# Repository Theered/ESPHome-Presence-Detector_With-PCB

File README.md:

# ESPHome-Presence-Detector_With-PCB
I was tired of my lights constantly turning off whenever I sat still while using a standard PIR motion detector. Since PIR sensors only detect "big movements", they often fail to notice someone who is sitting quietly.

To solve this, I built a presence detector using an mmWave sensor. Unlike a traditional PIR sensor, an mmWave sensor can detect very small movements, such as your chest moving while breathing, allowing it to reliably detect occupancy even when you're not moving around.

While designing the project, I decided to add a few extra features:

* **mmWave presence detection** for reliable occupancy sensing
* **PIR motion sensor** for fast motion detection when entering the room
* **Ambient light sensor** to prevent lights from turning on when the room is already bright
* **Status LED** to indicate Wi-Fi or device issues
* **Custom PCB** to keep the wiring clean and make assembly easier

The PCB connects all modules directly to the microcontroller, making installation as simple as plugging the sensors into their designated headers.

Sensor data is sent to Home Assistant using ESPHome, allowing you to create virtually any automation you can think of —from automatically controlling lights to sending notifications when someone enters a room, everything is possible.

## Requirements

Before starting this project, you will need:

1. A working Home Assistant server
2. A soldering iron and basic soldering skills
3. A bit of patience and a good mood ;)

**Note:** The status LED and its resistor are small and can be quite challenging to solder. If you don't care about the LED, it can be left out.

## PCB Design

schematic:

PCB:

## Design Inspiration

I wanted a clean and modern design for the detector, so i kindly asked chatGPT to make a few diffrent designes and shapes before settling on this final version:

i then started modeling my own...

## Project Status

🚧 This project is still under development.

Additional documentation will be added soon, including:

* Complete assembly guide
* ESPHome configuration- and firmware instalation guide
* refined 3D-printable enclosure files

Thank you for your patience while I finish building and documenting the project.

BOM:
1. ws2812b LED

2. TSL2591 IIC I2C Light Sensor

3. ESP32 S3 C3 SuperMini Development Board

5. HLK-LD2410c module

7. AM312 PIR motion detector

8. Female Straight Needle Pin Header

9. Custom PCB (gerber files are linked in the project)

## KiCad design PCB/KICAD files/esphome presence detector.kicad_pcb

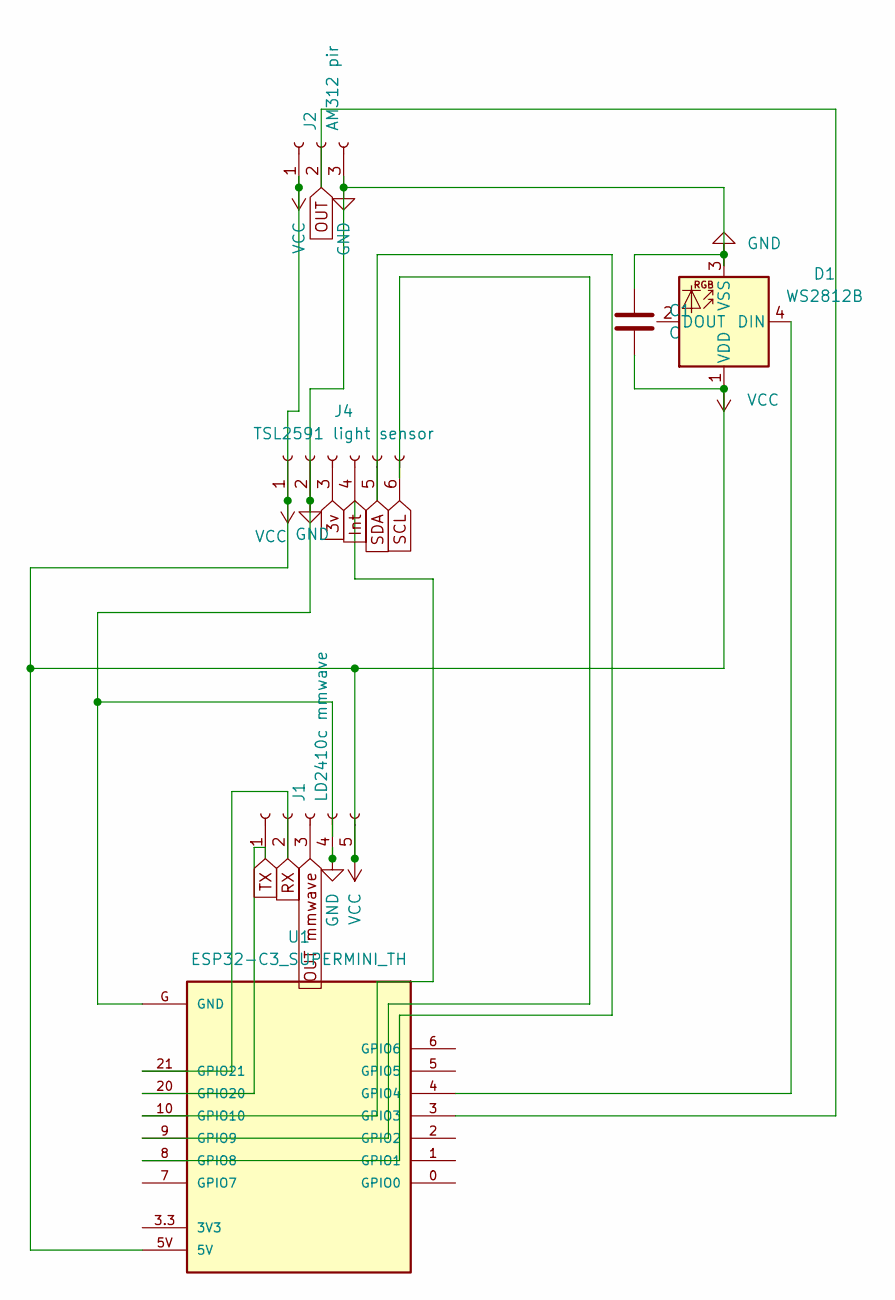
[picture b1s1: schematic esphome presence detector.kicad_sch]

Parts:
C1: C; C_0805_2012Metric_Pad1.18x1.45mm_HandSolder
D1: WS2812B; LED_WS2812B_PLCC4_5.0x5.0mm_P3.2mm
J1: LD2410c mmwave; PinSocket_1x05_P2.54mm_Vertical
J2: AM312 pir; PinSocket_1x03_P2.54mm_Vertical
J4: TSL2591 light sensor; PinSocket_1x06_P2.54mm_Vertical
U1: ESP32-C3_SUPERMINI_TH; MODULE_ESP32-C3_SUPERMINI_TH

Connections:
3v: J4.3
GND: C1.1, D1.3 (VSS), J1.4, J2.3, J4.2, U1.G (GND)
Int: J4.4, U1.10 (GPIO10)
unnamed: D1.4 (DIN), U1.4 (GPIO4)
OUT: J2.2, U1.3 (GPIO3)
OUT mmwave: J1.3
RX: J1.2, U1.21 (GPIO21)
SCL: J4.6
SDA: J4.5, U1.8 (GPIO8)
TX: J1.1, U1.20 (GPIO20)
VCC: C1.2, D1.1 (VDD), J1.5, J2.1, J4.1, U1.5V

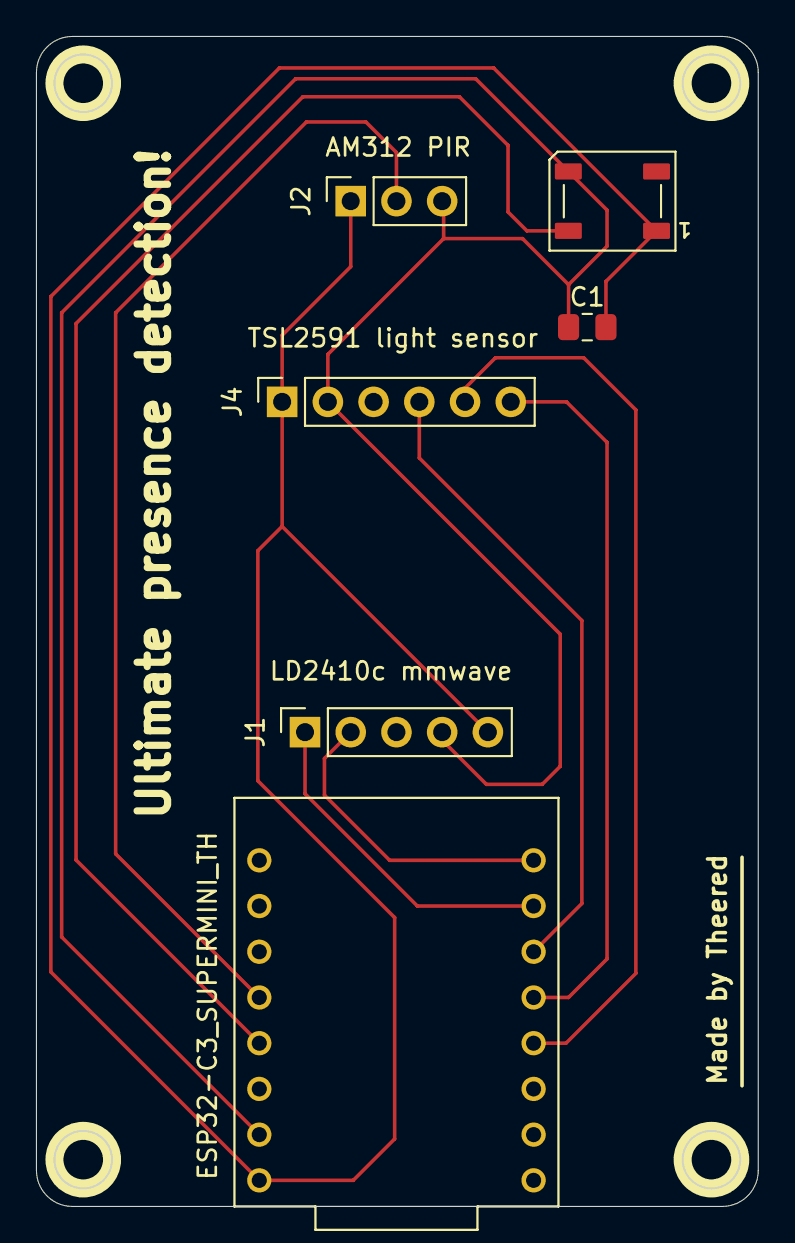
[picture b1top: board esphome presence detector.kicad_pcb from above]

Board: 2 copper layers, 40.1 x 64.9 mm, 6 parts (0 on the bottom side), 8 nets.

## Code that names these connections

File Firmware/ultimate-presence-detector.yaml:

# Board: ESP32-C3 Super Mini (Generic)
# Definition: definitions/boards/esp32-c3-supermini/manifest.yaml

substitutions:
  name: ultimate-presence-detector
  friendly_name: "Ultimate Presence Detector"
  
  # Pin Assignments
  pir_pin: GPIO3
  ws2812b_pin: GPIO4
  
  # I2C Pins (for TSL2591)
  i2c_sda: GPIO8
  i2c_scl: GPIO9
  
  # UART Pins (for LD2410C)
  ld2410_tx: GPIO21
  ld2410_rx: GPIO20

esphome:
  name: ${name}
  friendly_name: ${friendly_name}

esp32:
  variant: esp32c3
  flash_size: 4MB
  framework:
    type: esp-idf

logger:

api:
  encryption:
    key: "F7ViIO5/M8LV/Ve67E9GfHh85xXAf8uFSmWfIdFQUXo="

ota:
  - platform: esphome

wifi:
  ssid: !secret wifi_ssid
  password: !secret wifi_password
  ap:
    ssid: "Ultimate Presence Fallback"
    password: "ultimatepresence"

captive_portal:

# Component Buses
i2c:
  sda: ${i2c_sda}
  scl: ${i2c_scl}
  scan: true

uart:
  id: uart_bus
  tx_pin: ${ld2410_tx}
  rx_pin: ${ld2410_rx}
  baud_rate: 256000

ld2410:

binary_sensor:
  # AM312 PIR
  - platform: gpio
    pin: ${pir_pin}
    name: "PIR Motion"
    device_class: motion

  # LD2410
  - platform: ld2410
    has_target:
      name: "LD2410 Presence"
    has_moving_target:
      name: "LD2410 Moving Target"
    has_still_target:
      name: "LD2410 Still Target"

sensor:
  # TSL2591 Light Sensor
  - platform: tsl2591
    name: "Illuminance"
    id: tsl2591_illuminance
    address: 0x29
    update_interval: 60s
    full_spectrum:
      name: "Full Spectrum"
    infrared:
      name: "Infrared"
    visible:
      name: "Visible Light"

  # LD2410
  - platform: ld2410
    moving_distance:
      name: "Moving Distance"
    still_distance:
      name: "Still Distance"
    moving_energy:
      name: "Moving Energy"
    still_energy:
      name: "Still Energy"
    detection_distance:
      name: "Detection Distance"

# WS2812B Status LED
light:
  - platform: esp32_rmt_led_strip
    chipset: WS2812
    rgb_order: GRB
    pin: ${ws2812b_pin}
    num_leds: 1
    name: "Status LED"
    id: status_led

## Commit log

2026-06-15 Add LICENSE file with CC BY-NC 4.0
    Added Creative Commons Attribution-NonCommercial 4.0 International Public License to the project.
2026-06-29 Add schematic image to README
